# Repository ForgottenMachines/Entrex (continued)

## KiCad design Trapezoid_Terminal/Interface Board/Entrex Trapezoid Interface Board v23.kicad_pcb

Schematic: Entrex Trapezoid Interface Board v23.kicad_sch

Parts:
C1, C22, C23, C24, C25, C26: 221J03; C_Disc_D4.7mm_W2.5mm_P5.00mm
C2, C27, C101: 0.1UF-0603-25V-5%; C_Disc_D4.7mm_W2.5mm_P5.00mm
C3, C4, C5, C6, C7, C8, C9, C10, C11, C12, C13, C14, C15, C16, C17: Y5F; C_Disc_D4.7mm_W2.5mm_P5.00mm
C18, C19, C20, C21: C_Polarized; CP_Axial_L18.0mm_D6.5mm_P25.00mm_Horizontal
C28: 0.1UF-0603-25V-5%; C_Disc_D3.8mm_W2.6mm_P2.50mm
D1: 1N4001; D_DO-41_SOD81_P10.16mm_Horizontal
DPLX_sw_SG1, DPLX_sw_SG2: SW_SPDT
P15: Conn_02x40_Odd_Even_Shielded; 80 pin Edge Finger Connector
R0, R21, R22, R23, R1000: 330R; R_Axial_DIN0207_L6.3mm_D2.5mm_P10.16mm_Horizontal; Manufacturer_Part_Number YR1B24K9CC; Mouser Part Number 279-YR1B24K9CC
R2, R3, R4, R5, R6, R7: 220R; R_Axial_DIN0207_L6.3mm_D2.5mm_P10.16mm_Horizontal; Manufacturer_Part_Number YR1B24K9CC; Mouser Part Number 279-YR1B24K9CC
R8, R9, R10, R11, R12, R13, R14, R17: 1K; R_Axial_DIN0207_L6.3mm_D2.5mm_P10.16mm_Horizontal; Manufacturer_Part_Number YR1B24K9CC; Mouser Part Number 279-YR1B24K9CC
R15, R20: YR1B24K9CC; R_Axial_DIN0207_L6.3mm_D2.5mm_P10.16mm_Horizontal; Manufacturer_Part_Number YR1B24K9CC; Mouser Part Number 279-YR1B24K9CC
R16, R18: 1k; R_Axial_DIN0207_L6.3mm_D2.5mm_P10.16mm_Horizontal; Manufacturer_Part_Number YR1B24K9CC; Mouser Part Number 279-YR1B24K9CC
R19: 10K; R_Axial_DIN0207_L6.3mm_D2.5mm_P10.16mm_Horizontal; Manufacturer_Part_Number YR1B24K9CC; Mouser Part Number 279-YR1B24K9CC
R101: 150R; R_Axial_DIN0207_L6.3mm_D2.5mm_P10.16mm_Horizontal; Manufacturer_Part_Number YR1B24K9CC; Mouser Part Number 279-YR1B24K9CC
SW1: SW_DIP_x08; DIP-16_W7.62mm_Socket
UA1, UA2: P8212; DIP-24_W15.24mm
UA3, UA4: 8274N; DIP-16_W7.62mm
UA5: 74LS76; DIP-16_W7.62mm
UA6: SN74LS00N; DIP-14_W7.62mm
UA7: SN74LS10N; DIP-14_W7.62mm
UA8: SN74LS74AN; DIP-14_W7.62mm
UB3: 74173; DIP-16_W7.62mm
UB4: SN74LS51N; DIP-14_W7.62mm
UB5: SN74LS74AN; DIP-14_W7.62mm
UB6: SN74LS08N; DIP-14_W7.62mm
UB7: SN74LS04N; DIP-14_W7.62mm
UB8: SN74LS00N; DIP-14_W7.62mm
UC1: N8T98N; DIP-16_W7.62mm
UC2: SN74LS04N; DIP-14_W7.62mm
UC3: 74173; DIP-16_W7.62mm
UC4: 9324N; DIP-16_W7.62mm
UC5: SN75113N; DIP-16_W7.62mm; Manufacturer_Part_Number SN75113NE4
UC6: SN74LS00N; DIP-14_W7.62mm
UC7, UC8: SN74LS74AN; DIP-14_W7.62mm
UD1: SN7406N; DIP-14_W7.62mm
UD3: N8273N; DIP-16_W7.62mm
UD5, UD6: SN75115N; DIP-16_W7.62mm; Manufacturer_Part_Number SN75115N
UD7: SN74LS08N; DIP-14_W7.62mm
UD8: SN74LS04N; DIP-14_W7.62mm
UE1, UE2: SN7406N; DIP-14_W7.62mm
UE3: SN74LS74AN; DIP-14_W7.62mm
UE4: N8T97N; DIP-16_W7.62mm
UE5: SN75113N; DIP-16_W7.62mm; Manufacturer_Part_Number SN75113NE4
UE6: SN75115N; DIP-16_W7.62mm; Manufacturer_Part_Number SN75115N
UE7: SN74LS10N; DIP-14_W7.62mm
UE8: 74LS160; DIP-16_W7.62mm
UF1: Q2T2222; DIP-14_W7.62mm
UF2, UF4: SN74LS74AN; DIP-14_W7.62mm
UF3, UF6: SN74LS00N; DIP-14_W7.62mm
UF5: SN74LS08N; DIP-14_W7.62mm
UF7: SN74LS20N; DIP-14_W7.62mm
UF8: 74LS175; DIP-16_W7.62mm

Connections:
/U44P5: R18.1, UE8.1 (~MR)
/XX(UA2P11): UA2.11 (Strobe)
/XX(UA2P23): UA2.23 (~INT)
/XX(UA5P10): UA5.10 (~Q)
/XX(UA5P14): UA5.14 (~Q)
/XX(UB3P9): UB3.9 (~G1)
/XX(UB3P10): UB3.10 (~G2)
/XX(UB5P5): UB5.5 (Q)
/XX(UC1P1): UC1.1 (DIS4)
/XX(UC1P9): UC1.9 (~Out4)
/XX(UC3P9): UC3.9 (~G1)
/XX(UC3P10): UC3.10 (~G2)
/XX(UC3P15): UC3.15 (R)
/XX(UC4P1): UC4.1 (~E)
/XX(UC4P2): UC4.2 (A__B)
/XX(UC4P15): UC4.15 (A__B)
/XX(UC7P5): UC7.5 (Q)
/XX(UC7P8): UC7.8 (~Q)
/XX(UC7P12): UC7.12 (D)
/XX(UD3P4): UD3.4 (Q9)
/XX(UD3P5): UD3.5 (Q10)
/XX(UD3P6): UD3.6 (Clock_1)
/XX(UD3P9): UD3.9 (~Reset)
/XX(UD5P2): UD5.2 (1YP_(Sink))
/XX(UD5P6): UD5.6 (1RT)
/XX(UD5P10): UD5.10 (2RT)
/XX(UD5P12): UD5.12 (2RTC)
/XX(UD5P14): UD5.14 (2YP_(Sink))
/XX(UD6P2): UD6.2 (1YP_(Sink))
/XX(UD6P6): UD6.6 (1RT)
/XX(UD6P10): UD6.10 (2RT)
/XX(UD6P14): UD6.14 (2YP_(Sink))
/XX(UE1P8): UE1.8
/XX(UE1P9): UE1.9
/XX(UE1P12): UE1.12
/XX(UE1P13): UE1.13
/XX(UE3P6): UE3.6 (~Q)
/XX(UE3P8): UE3.8 (~Q)
/XX(UE4P9): UE4.9 (Out4)
/XX(UE4P10): UE4.10 (In4)
/XX(UF2P8): UF2.8 (~Q)
/XX(UF3P9): UF3.9
/XX(UF3P10): UF3.10
/XX(UF4P6): UF4.6 (~Q)
/XX(UF4P8): UF4.8 (~Q)
/XXUE6P2: UE6.2 (1YP_(Sink))
/XXUE6P14: UE6.14 (2YP_(Sink))
/unconnected-(SW1-Pad10): SW1.10
D1P1: UC2.6, UC6.4
GND: C1.2, C2.2, C3.2, C4.2, C5.2, C6.2, C7.2, C8.2, C9.2, C10.2, C11.2, C12.2, C13.2, C14.2, C15.2, C16.2, C17.2, C18.2, C19.2, C20.2, C21.2, C22.1, C23.1, C24.1, C25.2, C26.1, C27.2, C28.2, C101.2, D1.2 (A), DPLX_sw_SG1.2 (B), DPLX_sw_SG2.2 (B), P15.1, P15.2, R21.2, SW1.1, SW1.2, SW1.3, SW1.4, SW1.5, UA1.12 (GND), UA2.12 (GND), UA3.4 (D9), UA3.8 (GND), UA4.8 (GND), UA5.13 (GND), UA6.7 (GND), UA7.7 (GND), UA8.2 (D), UA8.7 (GND), UB3.8 (GND), UB3.15 (R), UB4.7 (GND), UB5.7 (GND), UB6.7 (GND), UB7.7 (GND), UB8.7 (GND), UC1.8 (GND), UC2.7 (GND), UC3.8 (GND), UC4.8 (GND), UC5.8 (GND), UC6.7 (GND), UC7.2 (D), UC7.7 (GND), UC7.11 (C), UC8.7 (GND), UD1.7 (GND), UD3.8 (GND), UD5.8 (GND), UD6.8 (GND), UD7.7 (GND), UD8.7 (GND), UE1.7 (GND), UE2.7 (GND), UE3.7 (GND), UE4.8 (GND), UE5.8 (GND), UE6.8 (GND), UE7.7 (GND), UE8.4 (P1), UE8.5 (P2), UE8.6 (P3), UE8.8 (GND), UF1.3 (E), UF1.5 (E), UF1.10 (E), UF1.12 (E), UF2.7 (GND), UF3.7 (GND), UF4.2 (D), UF4.7 (GND), UF4.12 (D), UF5.7 (GND), UF6.7 (GND), UF7.7 (GND), UF8.8 (GND)
P15_5: P15.5, UA1.22 (DI8), UA2.22 (DI8), UA3.3 (D8), UA4.3 (D8), UA5.9 (J)
P15_7: P15.7, UA1.20 (DI7), UA2.20 (DI7), UA3.2 (D7), UA4.2 (D7), UA5.12 (K)
P15_8: P15.8, UE4.1 (DIS4), UE4.15 (DIS2)
P15_9: P15.9, UA1.18 (DI6), UA2.18 (DI6), UA3.1 (D6), UA4.1 (D6), UA5.4 (J)
P15_10: P15.10, UC1.15 (DIS2)
P15_11: P15.11, UA1.16 (DI5), UA2.16 (DI5), UA3.15 (D5), UA4.15 (D5), UA5.16 (K)
P15_12: C1.1, P15.12, UA8.11 (C), UB3.1 (M), UB3.2 (N), UB6.12, UC2.5, UC3.1 (M), UC3.2 (N)
P15_13: P15.13, UA1.9 (DI4), UA2.9 (DI4), UA3.14 (D4), UA4.14 (D4), UE7.4, UF3.1
P15_14: P15.14, R3.2, UC1.6 (In3)
P15_15: P15.15, UA1.7 (DI3), UA2.7 (DI3), UA3.13 (D3), UA4.13 (D3), UF6.12
P15_16: P15.16, R2.2, UC1.10 (In4)
P15_17: P15.17, UA1.5 (DI2), UA2.5 (DI2), UA3.12 (D2), UA4.12 (D2), UF6.9
P15_18: P15.18, R4.2, UC1.12 (In5)
P15_19: P15.19, UA1.3 (DI1), UA2.3 (DI1), UB4.2, UB4.13, UC2.9, UF3.5
P15_20: P15.20, R5.2, UC1.4 (In2)
P15_21: P15.21, UB3.3 (Q0), UE4.13 (Out6)
P15_22: P15.22, R6.1, UC1.14 (In6)
P15_23: P15.23, UB3.4 (Q1), UE4.11 (Out5)
P15_24: P15.24, R7.1, UC1.2 (In1)
P15_25: P15.25, UB3.5 (Q2)
P15_26: P15.26, UE2.4
P15_27: P15.27, UB3.6 (Q3), UC1.7 (~Out3)
P15_28: P15.28, UC2.1
P15_29: P15.29, UC1.11 (~Out5), UC3.3 (Q0)
P15_30: P15.30, UB7.1
P15_31: P15.31, UC1.5 (~Out2), UC3.4 (Q1), UE4.7 (Out3)
P15_32: P15.32, UB7.3, UF4.3 (C)
P15_33: P15.33, UC1.13 (~Out6), UC3.5 (Q2), UE4.5 (Out2)
P15_34: P15.34, UA1.1 (~DS1)
P15_35: P15.35, UC1.3 (~Out1), UC3.6 (Q3), UE4.3 (Out1)
P15_36: P15.36, UA2.1 (~DS1)
P15_37: P15.37, UC5.3 (1YS), UC5.4 (1YP)
P15_38: P15.38, UC5.12 (2YP), UC5.13 (2YS)
P15_39: P15.39, UC5.1 (1ZP), UC5.2 (1ZS)
P15_40: P15.40, UC5.14 (2ZS), UC5.15 (2ZP)
P15_41: P15.41, UD6.11 (2B)
P15_42: P15.42, UD6.9 (2A)
P15_43: P15.43, UD5.7 (1A)
P15_44: P15.44, UD5.9 (2A)
P15_45: P15.45, UD5.5 (1B)
P15_46: P15.46, UD5.11 (2B)
P15_47: DPLX_sw_SG1.1 (A), P15.47, R14.2, UD8.13
P15_48: DPLX_sw_SG1.3 (C), P15.48, R13.2, UD8.1
P15_49: P15.49, UD6.7 (1A)
P15_50: P15.50, UD6.5 (1B)
P15_51: P15.51, UE6.7 (1A)
P15_52: P15.52, UE6.9 (2A)
P15_53: P15.53, UE6.11 (2B)
P15_54: P15.54, UE6.5 (1B)
P15_55: P15.55, UE5.12 (2YP), UE5.13 (2YS)
P15_56: P15.56, UE5.3 (1YS), UE5.4 (1YP)
P15_57: P15.57, UE5.14 (2ZS), UE5.15 (2ZP)
P15_58: P15.58, UE5.1 (1ZP), UE5.2 (1ZS)
P15_59: P15.59, UD1.12
P15_60: P15.60, UD1.2
P15_61: P15.61, UD1.4
P15_62: P15.62, UD1.10
P15_63: P15.63, UD1.6
P15_64: P15.64, UC2.13, UE7.12
P15_65: P15.65, UD1.8
P15_66: P15.66, UC2.11, UF6.3
P15_67: P15.67, UE2.8
P15_68: P15.68, UF6.6
P15_69: P15.69, UE2.6
P15_70: P15.70, UE1.6
P15_71: P15.71, UE2.10
P15_72: P15.72, UE1.10
P15_75: P15.75, UE1.4
P15_76: P15.76, UE2.12
P15_77: P15.77, UE1.2
P15_78: P15.78, UE2.2
P15_79: P15.79, UB6.9
U44P12: UB6.1, UC6.6
UA1_8: UA1.8 (DO3), UD1.1
UA1_17: UA1.17 (DO6), UD1.11
UA8_4: UA8.4 (~S), UA8.9 (Q)
VCC: C2.1, C3.1, C4.1, C5.1, C6.1, C7.1, C8.1, C9.1, C10.1, C11.1, C12.1, C13.1, C14.1, C15.1, C16.1, C17.1, C18.1, C19.1, C20.1, C21.1, C27.1, C28.1, P15.3, P15.4, R2.1, R3.1, R4.1, R5.1, R6.2, R7.2, R8.2, R9.2, R10.2, R11.2, R12.2, R13.1, R14.1, R15.2, R16.2, R17.2, R18.2, R19.2, R20.2, R22.2, UA1.2 (Mode), UA1.13 (DS2), UA1.24 (VCC), UA2.2 (Mode), UA2.13 (DS2), UA2.24 (VCC), UA3.5 (D10), UA3.10 (S0), UA3.16 (VCC), UA4.5 (D10), UA4.10 (S0), UA4.16 (VCC), UA5.2 (~S), UA5.5 (VCC), UA5.7 (~S), UA6.14 (VCC), UA7.14 (VCC), UA8.1 (~R), UA8.12 (D), UA8.14 (VCC), UB3.16 (VCC), UB4.9, UB4.14 (VCC), UB5.4 (~S), UB5.10 (~S), UB5.14 (VCC), UB6.14 (VCC), UB7.14 (VCC), UB8.14 (VCC), UC1.16 (VCC), UC2.14 (VCC), UC3.16 (VCC), UC4.16 (VCC), UC5.16 (VCC), UC6.14 (VCC), UC7.14 (VCC), UC8.14 (VCC), UD1.14 (VCC), UD3.16 (VCC), UD5.16 (VCC), UD6.16 (VCC), UD7.14 (VCC), UD8.14 (VCC), UE1.14 (VCC), UE2.14 (VCC), UE3.4 (~S), UE3.10 (~S), UE3.14 (VCC), UE4.16 (VCC), UE5.16 (VCC), UE6.16 (VCC), UE7.14 (VCC), UE8.3 (P0), UE8.16 (VCC), UF2.4 (~S), UF2.10 (~S), UF2.12 (D), UF2.14 (VCC), UF3.14 (VCC), UF4.14 (VCC), UF5.14 (VCC), UF6.14 (VCC), UF7.14 (VCC), UF8.16 (VCC)
XX(UF3P8): UF3.8
u1_3: R16.1, UA8.3 (C), UB8.9, UD5.1 (1YS_(Pullup)), UD8.5, UE6.1 (1YS_(Pullup))
u1_6: UA8.6 (~Q), UD7.10
u1_8: UA8.8 (~Q), UC6.5
u2_1: UB8.1, UC8.6 (~Q)
u2_2: UB8.2, UB8.4, UC2.4
u2_3: UB6.2, UB8.3
u2_5: UB8.5, UC8.5 (Q)
u2_6: UA8.13 (~R), UB8.6
u2_10: UB8.10, UB8.12, UD8.9, UE8.15 (Tc)
u2_13: UB8.13, UC6.13, UC7.3 (C), UD8.6, UF7.1
u3_1: UB6.11, UC8.1 (~R)
u3_2: UC8.2 (D), UC8.4 (~S)
u3_3: UB8.11, UC2.3, UC8.3 (C)
u3_8: UC8.8 (~Q), UE7.9, UE8.9 (~Pe)
u3_9: UC8.9 (Q), UC8.13 (~R)
u3_10: UC8.10 (~S), UD8.8
u3_12: R15.1, UC8.12 (D), UD3.10 ("D"_Input), UD5.15 (2YS_(Pullup)), UD6.1 (1YS_(Pullup))
u4_2: UD7.1, UD8.2, UE5.9 (CC), UE6.3 (1STRB), UE6.13 (2STRB), UF1.7 (C)
u4_3: R17.1, UA7.9, UD6.15 (2YS_(Pullup)), UD8.3, UE6.15 (2YS_(Pullup)), UE7.10
u4_4: UC8.11 (C), UD8.4, UE8.2 (CK)
u4_10: UC5.10 (2C), UD8.10, UE5.7 (1C)
u4_11: UC6.3, UD8.11
u4_12: UC5.9 (CC), UD5.3 (1STRB), UD6.13 (2STRB), UD7.12, UD8.12, UF1.1 (C)
u6-2: UF6.1, UF8.2 (Q0)
u6-10: UF7.4, UF8.10 (Q2)
u6_3: UF5.2, UF8.3 (~Q0)
u6_6: UF5.1, UF8.6 (~Q1)
u6_7: UF6.4, UF8.7 (Q1)
u6_12: UF7.8, UF8.12 (D2)
u6_13: UF2.2 (D), UF5.6, UF8.13 (D3)
u7-2: UA7.2, UB7.4
u7-13: UA7.3, UA7.13, UB7.13, UD7.5, UF3.13, UF4.11 (C), UF7.6
u7_1: UA7.1, UA7.4, UB4.1, UB4.3, UB7.10
u7_5: UA7.5, UB7.2
u7_6: UA6.10, UA7.6, UF4.10 (~S)
u7_8: UA6.5, UA6.9, UA7.8
u7_10: UA7.10, UB7.12, UC6.2, UE4.6 (In3)
u7_12: UA6.4, UA7.12
u8_5: UB4.8, UB7.5
u8_6: UA4.11 (D1), UB7.6
u8_9: UB4.6, UB7.9
u8_11: UA3.7 (S1), UA4.7 (S1), UA7.11, UB4.4, UB4.10, UB7.11, UC7.4 (~S), UF3.11
u9_1: UC7.1 (~R), UF4.1 (~R), UF5.11
u9_9: UA4.4 (D9), UC7.9 (Q)
u9_13: UC7.13 (~R), UE7.6
u10_3: UD6.3 (1STRB), UD7.3
u10_4: UC6.11, UD7.4
u10_8: UD7.2, UD7.8, UD7.13
u10_9: UD7.6, UD7.9, UE7.11
u10_11: UD5.13 (2STRB), UD7.11
u11_1: UE7.1, UF8.15 (Q3)
u11_2: UE7.2, UF8.11 (~Q2)
u11_5: UA5.1 (C), UA5.6 (C), UC2.2, UE7.5, UF3.2, UF3.4, UF6.10, UF6.13
u11_8: UD3.7 (Clock_2), UE7.8
u11_13: UE7.13, UF5.3
u12_2: UC7.6 (~Q), UF7.2
u12_5: UC5.7 (1C), UE5.10 (2C), UF2.5 (Q), UF6.2, UF6.5, UF7.5
u13_1: UA6.1, UB6.6
u13_12: UA6.12, UE3.5 (Q), UE4.12 (In5)
u14_3: UB3.7 (CK), UB6.3, UC3.7 (CK), UF2.11 (C)
u14_4: UB5.8 (~Q), UB6.4
u14_5: UB5.6 (~Q), UB6.5
u15_8: UC5.5 (1A), UC5.6 (1B), UC6.8, UE5.11 (2A)
u15_9: UA6.11, UC6.9
u15_10: UA6.3, UC6.10
u15_12: UC6.12, UF2.6 (~Q)
u16_4: C22.2, UD6.4 (1RTC)
u16_12: C25.1, UD6.12 (2RTC)
u17_4: C23.2, UE6.4 (1RTC)
u17_12: C24.2, UE6.12 (2RTC)
u18_8: UF5.9, UF6.8
u18_11: UF6.11, UF8.1 (~Mr)
u20_2: UB3.14 (P0), UB5.2 (D), UD3.11 (Q1), UF8.5 (D1)
u20_3: UB5.3 (C), UB5.11 (C), UB8.8, UF2.3 (C), UF8.9 (Cp)
u20_10: UA6.13, UB5.9 (Q)
u22_4: C26.2, UD5.4 (1RTC)
u24_8: UF2.13 (~R), UF5.8
u25_6: UA4.6 (Serial_Out), UB4.5
u25_9: UA4.9 (Clock), UA6.6
u27_3: R8.1, SW1.12, UC4.3 (B0)
u27_4: R9.1, SW1.13, UC4.4 (B1)
u27_5: R10.1, SW1.14, UC4.5 (B2)
u27_6: R11.1, SW1.15, UC4.6 (B3)
u27_7: R12.1, SW1.16, UC4.7 (B4)
u27_9: UC3.11 (P3), UC4.9 (A4), UD3.3 (Q8)
u27_10: UC3.12 (P2), UC4.10 (A3), UD3.2 (Q7)
u27_11: UC3.13 (P1), UC4.11 (A2), UD3.1 (Q6)
u27_12: UC3.14 (P0), UC4.12 (A1), UD3.15 (Q5)
u27_13: UB3.11 (P3), UC4.13 (A0), UD3.14 (Q4)
u27_14: UC4.14 (A=B), UF5.4, UF5.5
u28_2: UE4.2 (In1), UF2.9 (Q)
u28_4: UC6.1, UE4.4 (In2), UF4.9 (Q)
u28_14: UA6.2, UE3.9 (Q), UE4.14 (In6)
u29_4: C101.1, R101.2, UF4.4 (~S)
u29_5: UF3.12, UF4.5 (Q)
u30_6: UA3.6 (Serial_Out), UC5.11 (2A), UE5.5 (1A), UE5.6 (1B)
u30_9: UA3.9 (Clock), UA6.8
u30_11: UA3.11 (D1), UB7.8
u31_12: UB3.12 (P2), UB5.12 (D), UD3.13 (Q3), UF8.4 (D0)
u33_12: UB3.13 (P1), UD3.12 (Q2), UF7.9, UF7.10, UF7.12, UF7.13
u34_2: UA5.11 (Q), UE3.2 (D)
u34_3: UC2.10, UE3.3 (C)
u34_11: UC2.12, UE3.11 (C)
u34_12: UA5.15 (Q), UE3.12 (D)
u34_13: UA1.14 (~CLR), UA2.14 (~CLR), UA5.3 (~R), UA5.8 (~R), UA8.10 (~S), UB5.1 (~R), UB5.13 (~R), UB6.8, UB6.13, UE3.1 (~R), UE3.13 (~R), UF2.1 (~R), UF4.13 (~R), UF5.10, UF5.12, UF5.13
u35_3: R101.1, UF3.3
u35_6: UC7.10 (~S), UF3.6
u36_4: UA2.4 (DO1), UE2.5
u36_6: UA2.6 (DO2), UE2.3
u36_8: UA2.8 (DO3), UE2.1
u36_10: UA2.10 (DO4), UE2.13
u36_15: UA2.15 (DO5), UE2.9
u36_17: UA2.17 (DO6), UE2.11
u36_19: UA2.19 (DO7), UE1.1
u36_21: UA2.21 (DO8), UE1.3
u37_8: UC2.8, UE7.3
u40_4: UA1.4 (DO1), UD1.5
u40_6: UA1.6 (DO2), UD1.3
u40_10: UA1.10 (DO4), UE1.5
u40_15: UA1.15 (DO5), UD1.9
u40_19: UA1.19 (DO7), UD1.13
u40_21: UA1.21 (DO8), UE1.11
u44_2: R1000.2, UF1.2 (B)
u44_6: R0.2, UF1.6 (B)
u44_8: R0.1, R22.1, R23.1, R1000.1, UF1.8 (C)
u44_9: R20.1, R21.1, UF1.9 (B)
u44_13: R23.2, UF1.13 (B)
u44_14: D1.1 (K), R19.1, UB6.10, UF1.14 (C)

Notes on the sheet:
Duplex Switch DPDT with CENTER OFF CG1 or CG2
All VCC & GND modules
Completely Unused
GND-VCC Capacitors
Strobe Input
Clock Input
Printer
UC7A Pin 6 inverse-Q latch
Unused
Data Trans
= Data Bus? = Keyboard = Processor Board = Floppy Disk Controller Board (FDC) = RAM Bus = I/O (Duplexer) Board = Printer
WARNING: Until refined & corrected, Global Label tag arrows may not indicate the proper signal in/out direction. IN was used as default when KiCad Symbols (components) were not clear on In vs Out signals, so always check component datasheets when in doubt.
Terminal Back I/O Plug "CG2"
UF4A Q latch
Backplane pins that are not connected to any other pins other than the backplane connector are not connected to the Backplane BUS. Neither are backplane pins whose multi-pin connections are otherwise represented with regular wires
Terminal Back I/O Plug "CG1"
= NC on Backplane
How to make u4_10 and u12_5 both go high?
Other Trans
UF7A four conditions
Data Input
Data Trans
Processor
KiCad Bus Range Creator https://bit.ly/KiCadBRC
UF2A pin 5 Q latch
I/O (Duplexer) Board
UF8 Pin 10 Q2
Strobe Input
Data Bus ?
All Points Start and End with Backplane Connector (P15)

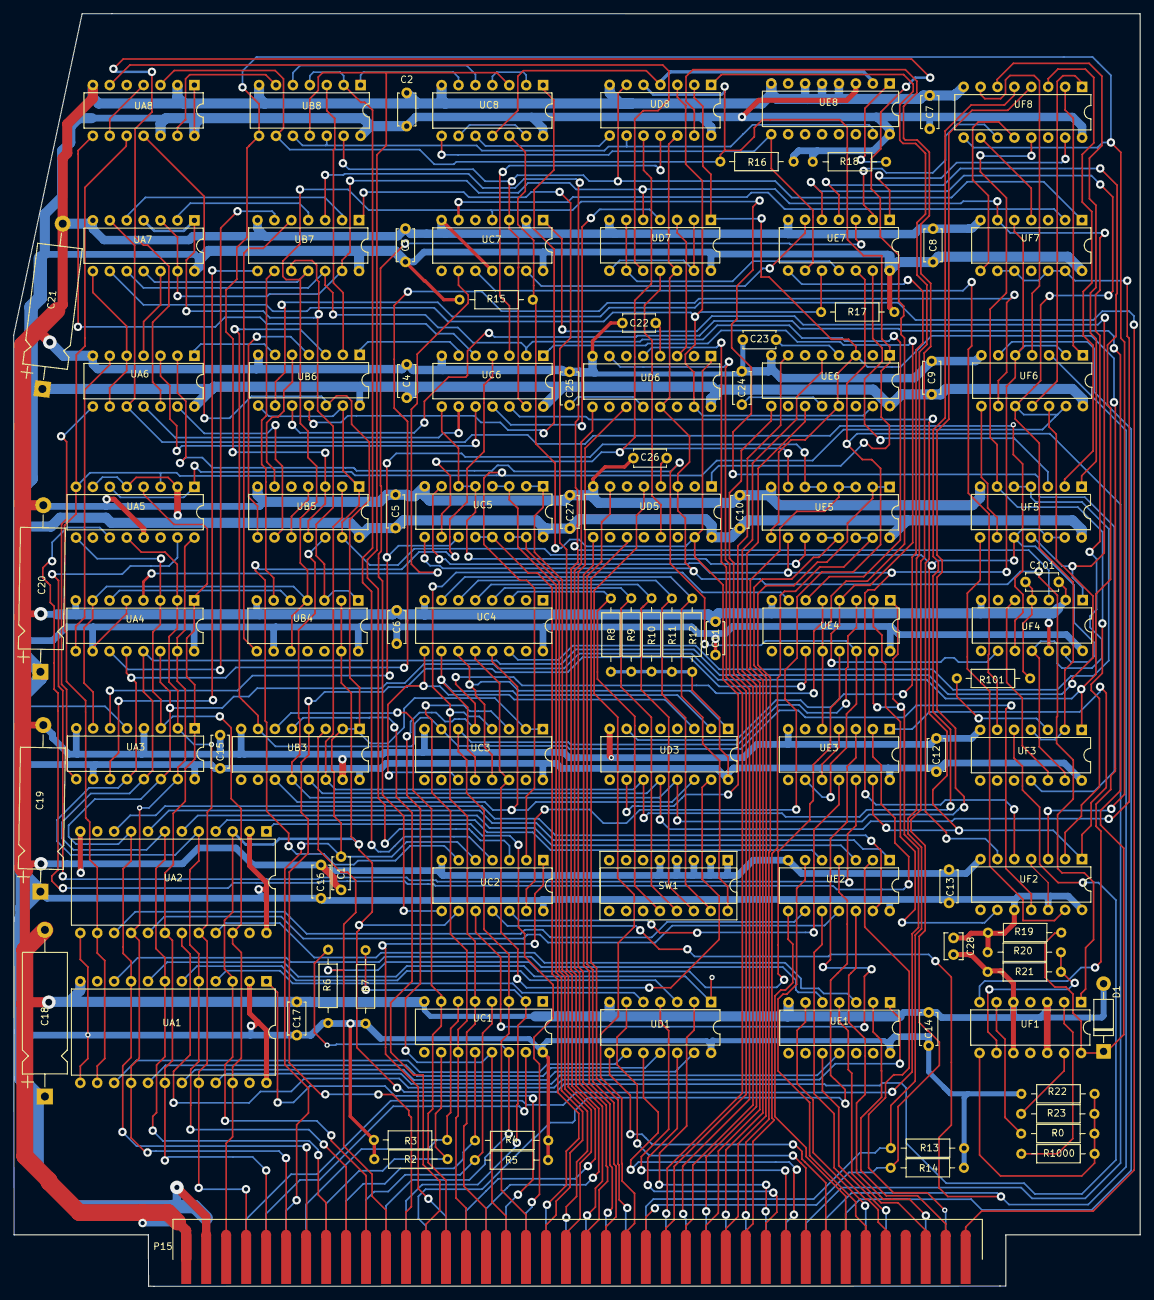
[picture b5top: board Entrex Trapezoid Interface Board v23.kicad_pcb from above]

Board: 2 copper layers, 169.1 x 191.0 mm, 101 parts (0 on the bottom side), 208 nets.

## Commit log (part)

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2023-04-18 J17_17
2023-04-18 just clicking save
2023-04-18 Changes since NetRenaming Split
2023-04-19 Add Keyboard Plug Mapping
2023-04-19 Backups
2023-04-20 1920 memory schematic
2023-04-23 fix interface board errors
2023-04-23 Add IO Testers
2023-04-23 i/o board improvements
2023-04-27 Rename Training-Overview Videos.txt to Training-Overview Videos URLs.txt
2023-04-27 notes
2023-04-28 UF5 pin 9 connection
2023-04-28 u34_13!
2023-04-29 add datasheets
2023-04-29 pictures
2023-04-30 IO Testing
2023-05-01 warnings
2023-05-01 Create Trebisky_interface_remap
2023-05-01 renames
2023-05-01 labels
2023-05-03 u19_16/u19_12
2023-05-03 pin4 on UA5
2023-05-03 74LS51
2023-05-03 Talk To Me
2023-05-06 corrections
2023-05-06 Backup Directory Superfluous
2023-05-07 bkups
2023-05-07 Directions
2023-05-07 talkey
2023-05-07 junk
2023-05-07 hunt
2023-05-07 datas
2023-05-07 Keyboard
2023-05-08 cleanup
2023-05-15 74LS160
2023-05-15 UB8P12
2023-05-15 u36_13
2023-05-16 74ls160a
2023-05-16 tweaks
2023-05-18 housekping
2023-05-19 IO Experiments
2023-05-19 RANDOM!
2023-05-19 UB5B Pin 11
2023-05-20 Corrections & Testing
2023-05-20 play
2023-05-20 code
2023-05-20 nothing
2023-05-21 testing
2023-05-21 tweaking
2023-05-22 Testing x2
2023-06-01 Fix Nets
2023-06-09 fixes
2023-07-10 Entrex Data/Scope PSU Board Build
2023-07-12 Place components
2023-07-16 Datasheet
2023-07-16 Resize pic
2023-07-16 progress
2023-07-16 building
2023-07-17 libraries
2023-07-17 Build
2023-07-18 More Build
2023-07-22 More Building
2023-07-22 buildout
2023-08-12 Build more
2023-11-07 main
2023-12-10 Add Pics
2023-12-10 pinouts
2023-12-11 jumper
2023-12-12 pics
2023-12-29 Add Images
2023-12-29 rotate
2023-12-31 resistors
2024-01-04 mpre
2024-01-04 diagnose
2024-01-15 clean
2024-01-15 fix?
2024-01-15 who knows
2024-02-05 Logo
2024-02-06 Image Arrange
2024-02-06 Setup
2024-02-06 Upwork Setup
2024-02-06 Holy ***
2024-02-06 PCB Image Borders Marking
2024-02-06 AMLDC-2044B - Omoding Pius v1
2024-02-06 Final before Schematic Picture Removal
2024-02-06 Begin Net Names assignments
2024-02-06 global labels
2024-02-07 Rogelio Pineda assigned Global Labels
2024-02-07 Chips Placed First Wave
2024-02-07 The Traces Have Begun!
2024-02-07 extra
2024-02-07 Alignments
2024-02-08 Rogelio Pineda's mid-day work
2024-02-08 Front Panel Magic
2024-02-09 Front Panel Entrex - Right Before Schematic Image Removal
2024-02-09 Just before Global Assign Footprints (Entrex Front Panel)
2024-02-09 Before mass-resistor footprint add & VCC/+5v label merge
2024-02-09 Add Scanner Board preliminarily
2024-02-10 Place Missing Chips
2024-02-10 Right before 1st board tracing picture removal and addition of second
2024-02-10 ready for AMLDC Front Board Tracing part 2
2024-02-11 Lots
2024-02-11 Before VCC to +5v conversion on Entrex Front Panel
2024-02-11 Tester begin
2024-02-11 Front Panel Tester
2024-02-11 more
2024-02-12 Trace Part 3
2024-02-15 Ready for Top p4
2024-02-16 Add Phar's Resources
2024-02-16 Final Tracing on Board Front - AMLDC
2024-02-16 Start Backside AMLDC
2024-02-16 Note on MPS6533-Motorola
2024-02-17 Integrate Phar's Schematics
2024-02-17 Trapezoid Interface
2024-02-17 same
2024-02-21 DRC Checks p1
2024-02-21 backside p2
2024-02-21 front panel tester DRC
2024-02-23 AMLDC - Right before switching card-edge from Disk to Tape
2024-02-23 AMLDC Ready for part 6
2024-02-24 Ready for AMLDC p8
2024-02-27 Draw 9
2024-02-29 part 9
2024-02-29 Schematic Prep
2024-03-01 schematic p2
2024-03-06 AMLDC work
2024-03-08 Hmmm
2024-03-08 part 5
2024-03-12 connect 5 review
2024-03-14 p6 setup
2024-03-16 front panel study
2024-03-22 construct 9
2024-03-25 SimH
2024-03-25 Scanner Board build 1
2024-03-25 Tape Controller
2024-03-25 Scanner Trace 2
2024-04-03 Disk Controller
2024-04-28 SomeComputerGuy's Arduino
2024-05-04 JoeZ Fixes the Trapezoid!!!!!
2024-05-14 Trapezoid Options
2024-05-14 undo
2024-05-15 Trapezoid Terminal Interface Corrections
2024-05-15 io testers depricated
2024-05-15 Controller
2024-05-15 misc
2024-05-25 superfluous backups
2024-05-25 trapezoid testing
2024-05-25 Rogelio Pineda - connect 9 AMLDC-2044B
2024-05-31 TRAPEZOID SCREEN CONTROL
2024-05-31 minor cursor control with confusion
2024-05-31 Cursor Magic 2
2024-05-31 Crazy Cursors
2024-06-01 Better cursor but
2024-06-02 Trapezoid Arduino KiCad
2024-06-03 Trapezoid Schematic comparisons
2024-06-03 AMLDC
2024-06-08 backup crap
2024-09-02 VCFMW
2024-12-15 Entrex Data/Scope VCF text display
2024-12-15 RR Screens
2024-12-15 RR scripts
2024-12-15 l]inx s]inc
2024-12-15 afdasdfafd
    dsfdafdasd
2024-12-15 retro recipes trapezoid
2025-01-03 tests
2025-01-03 clann[p
2025-01-04 Terminals
2025-05-03 Joe Verifies
2025-06-18 Create yni]o
2025-06-18 no keyboard
2025-09-09 VCFMW!
2025-09-12 V FFMW
2025-09-25 ORIGINAL DATASCOPE
2025-09-28 RENAME
2025-09-30 done 1
2025-09-30 too many backups
2025-10-01 Upgrades 3
